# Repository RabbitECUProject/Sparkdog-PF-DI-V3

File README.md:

# Sparkdog-PF-DI-V3
KiCad project for hardware development of Sparkdog PF-DI PCB. The Sparkdog PF-DI PCB can be used as a plug in PCB for the Rabbit ECU, extending the functionality to include:

MK10 processor
4 x Direct injection driver circuit
2 x knock input circuit
1 x 4-channel H-Bridge driver
4 VVT input channels in addition to the Rabbit ECU Crank/Cam inputs

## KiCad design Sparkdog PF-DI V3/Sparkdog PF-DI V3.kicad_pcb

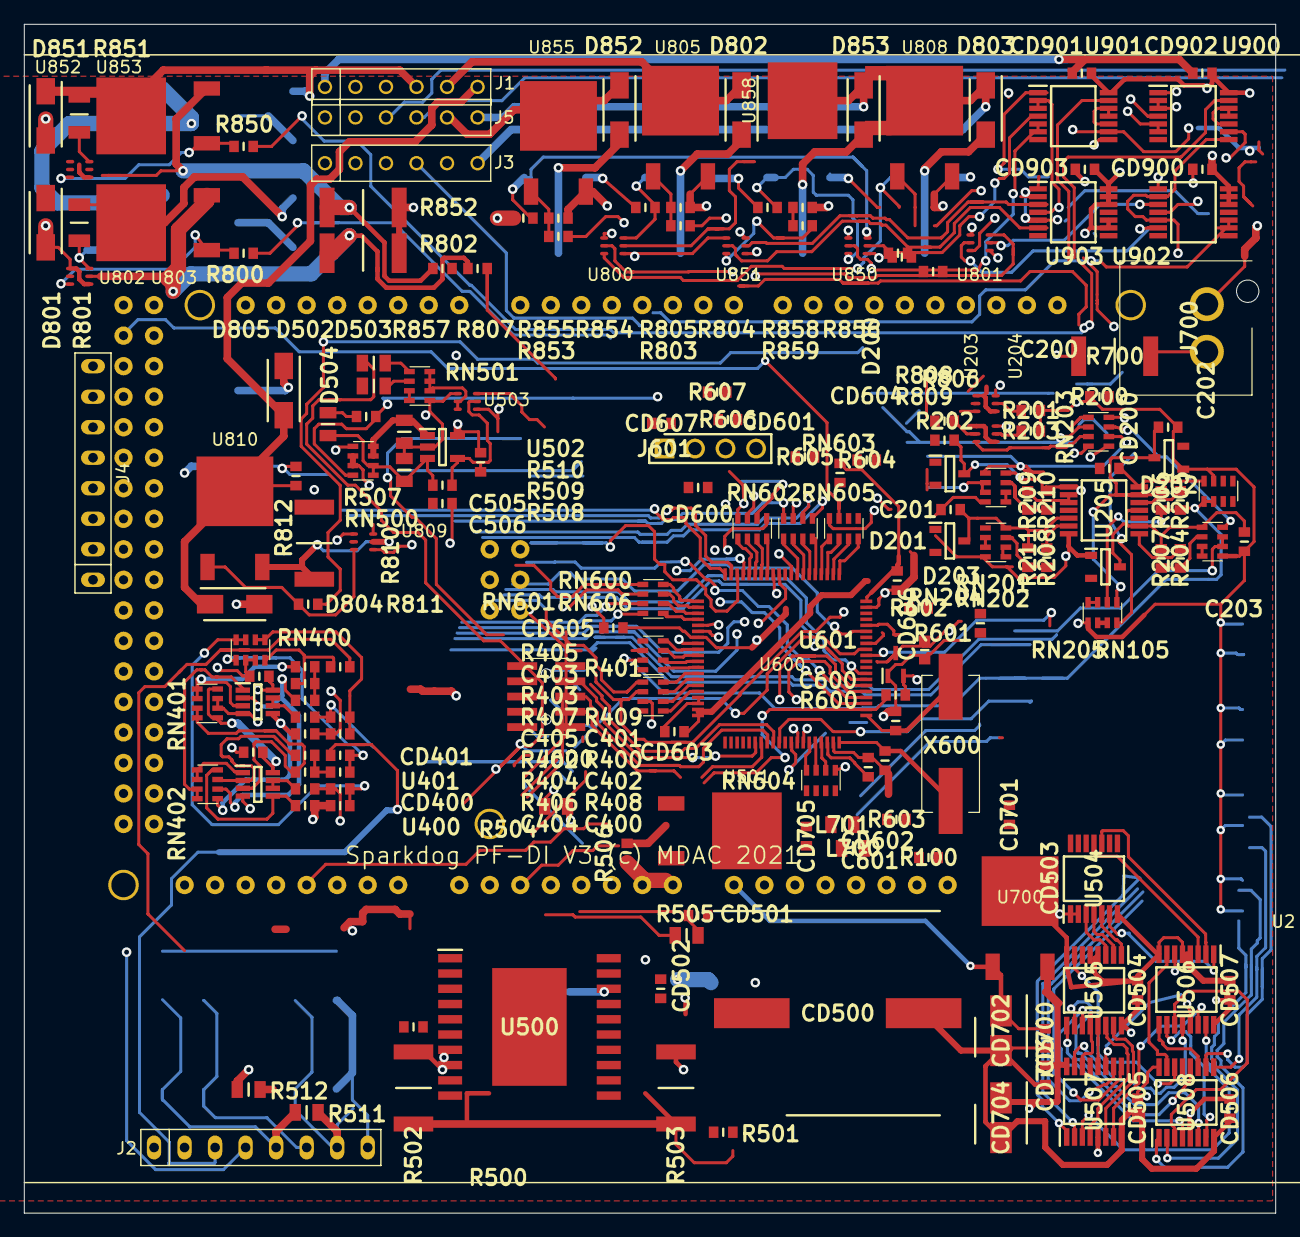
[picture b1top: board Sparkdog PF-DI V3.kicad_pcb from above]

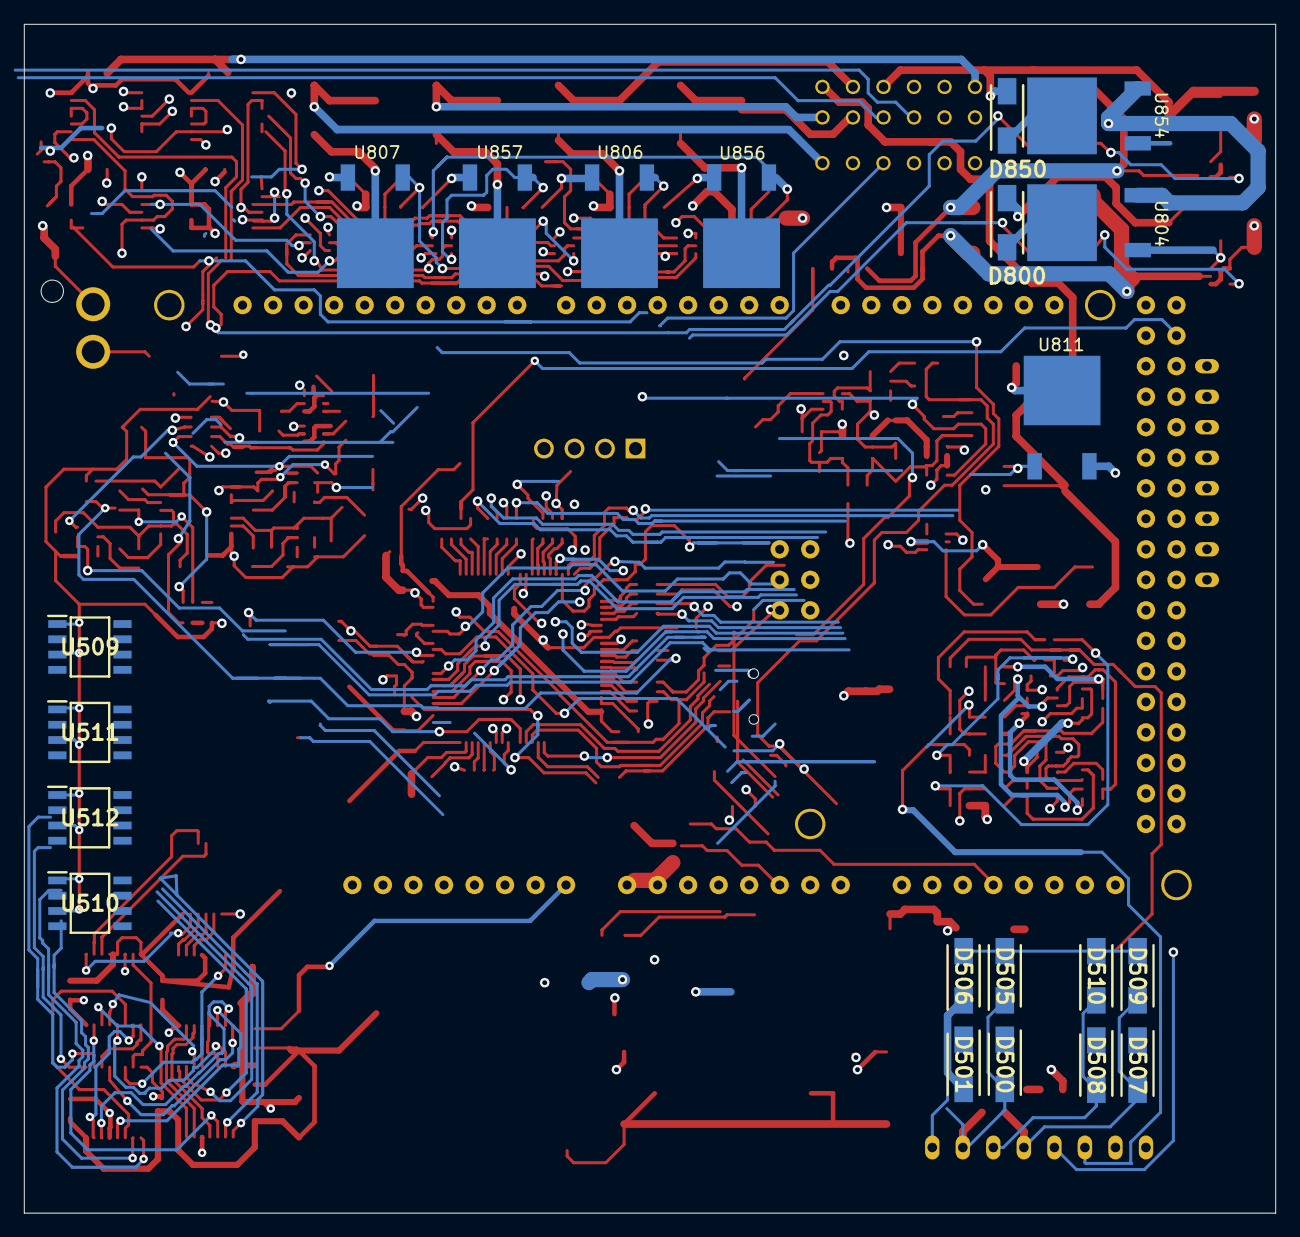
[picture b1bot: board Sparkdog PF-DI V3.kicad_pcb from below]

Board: 4 copper layers, 104.1 x 98.9 mm, 212 parts (21 on the bottom side), 251 nets.

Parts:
C200, C201, C202, C203, C402, C403, C404, C405: 0603 1nF; RESC1608X55N
C400, C401: 0603 100nF; RESC1608X55N
C505, C506: 0805 10uF; RESC2012X60N
C600, C601: 0603 10pF; RESC1608X55N
CD200, CD400, CD401, CD501, CD502, CD503, CD504, CD505, CD506, CD507, CD600, CD601, CD602, CD603, CD604, CD605, CD606, CD607, CD700, CD701, CD703, CD705, CD900, CD901, CD902, CD903: 0603 100nF; RESC1608X55N
CD500: CAP4mm 4.7uF; CAPAE1700X1700N
CD702, CD704: CAP4mm 4.7uF; CAPAE430X550N
D200, D201, D202, D203: BZX84C5V1LT1G; SOT96P237X111-3N
D500, D501, D505, D506, D507, D508, D509, D510: B120-E3; DIOM5127X229N
D502, D503, D504: 0805 1N4148; RESC2012X60N
D800, D802, D803, D805, D850, D852, D853: DO-214AC SCHOTTKY; DIOM5127X229N
D801, D804, D851: DO-214AC 81V; DIOM5127X229N
J1, J3, J5: Conn_01x06_Female; SIP-6
J2, J4: Conn_01x08_Female; SIP-8
J600: M50-3610542R; M503610542
J601: Conn_01x04; HDRV4W62P0X254_1X4_1016X240X949P
J700: Conn_01x02; 18772852
L700, L701: 0805 10nH; RESC2012X60N
R100, R204, R205, R206, R207, R208, R209, R210, R211, R602, R603, R604, R605: 0603 0R; RESC1608X55N
R200, R201, R202, R203, R406, R407, R408, R409, R600, R601, R807, R857: 0603 1k; RESC1608X55N
R400, R401, R804, R806, R854, R856: 0603 4.7k; RESC1608X55N
R402, R403, R404, R405, R507: 0603 47k; RESC1608X55N
R500, R501: 0603 100k; RESC1608X55N
R502, R503: 2512 0.1R; RESC6331X75N
R504, R505, R511, R512: 0805 0R; RESC2012X60N
R506, R803, R805, R808, R809, R812, R853, R855, R858, R859: 0603 10k; RESC1608X55N
R508: 0603 820k; RESC1608X55N
R509: 0603 5M; RESC1608X55N
R510: 0603 470k; RESC1608X55N
R606, R607: 0603 39R; RESC1608X55N
R700: 2512 1R; RESC6331X75N
R800, R850: 0603 470R; RESC1608X55N
R801, R851: 1206 4.7k; RESC3216X60N
R802, R852: 2512 0.05R; RESC6331X75N
R810: 2512 0.2R; RESC6331X75N
R811: 0603 220R; RESC1608X55N
RN105, RN604: 1206 1k; 742C083103JP
RN201, RN202, RN204, RN205, RN501, RN600, RN602, RN603, RN605, RN606: 1206 10k; 742C083103JP
RN203: 1206 470R; 742C083103JP
RN400, RN402: 220k; 742C083103JP
RN401: 220R; 742C083103JP
RN500: 1206 180k; 742C083103JP
RN601: 1206 100k; 742C083103JP
U2: Arduino_Footprint; ARDUINO_DUE
U203, U204: Dual_Trans_Array_PNP; SOT-363-6
U205: 74AHC14PW,118; SOP65P640X110-14N
U400, U401: TLV9052; SOT65P280X110-8N
U500: L298P; SOIC127P1420X360-21N
U501, U805, U806, U807, U808, U855, U856, U857, U858: SUD19P06-60; MDAC-TO-252-3
U502: TL331SN4T3G; SOT95P275X110-5N
U503, U809: Dual_Trans_Array_NPN; SOT-363-6
U504: SN74HCS164QPWRQ1; SOP65P640X120-14N
U505, U506: 74HC238PW-Q100J; SOP65P640X110-16N
U507, U508: CD4043BPWR; SOP65P640X120-16N
U509, U510, U511, U512: ZXMS6004DN8-13; SOIC127P600X175-8N
U600: MK10DX128VLK7
U601: TLV809EA29DCKR; SOT65P210X110-3N
U700: BD433M5FP-CE2; MDAC-TO-252-3
U800, U801, U802, U850, U851, U852: DDC113TU; SOT-363-6
U803, U804, U810, U811, U853, U854: STD7NK40Z; MDAC-TO-252-3
U900, U901: SN74AHCT02; SOP65P640X110-14N
U902, U903: SN74AHCT08; SOP65P640X110-14N
X600: Crystal; ECS49205PXTR

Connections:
/5 ETC/ETC_ENA: D502.2, R500.2, U600.52
/5 ETC/ETC_ENB: D503.2, R501.1, U600.71
/5 ETC/ETC_PEN: R506.2, U501.1, U503.6
/5 ETC/IO_PWM1: U509.7, U509.8
/5 ETC/IO_PWM2: U509.5, U509.6
/5 ETC/IO_PWM3: U510.7, U510.8
/5 ETC/IO_PWM4: U510.5, U510.6
/5 ETC/IO_PWM5: U511.7, U511.8
/5 ETC/IO_PWM6: U511.5, U511.6
/5 ETC/IO_PWM7: U512.7, U512.8
/5 ETC/IO_PWM8: U512.5, U512.6
/5 ETC/PIN1: U507.1, U509.2
/5 ETC/PIN2: U507.2, U509.4
/5 ETC/PIN3: U508.1, U510.2
/5 ETC/PIN4: U508.2, U510.4
/5 ETC/PIN5: U507.10, U511.2
/5 ETC/PIN6: U507.9, U511.4
/5 ETC/PIN7: U508.10, U512.2
/5 ETC/PIN8: U508.9, U512.4
/5 ETC/QA: U504.3, U505.3
/5 ETC/QB: U504.4, U505.2
/5 ETC/QC: U504.5, U505.1
/5 ETC/QD: U504.6, U506.1
/5 ETC/QE: U504.10, U506.2
/5 ETC/QF: U504.11, U506.3
/5 ETC/RES1: U506.15, U507.3
/5 ETC/RES2: U506.14, U507.7
/5 ETC/RES3: U506.13, U507.11
/5 ETC/RES4: U506.12, U507.15
/5 ETC/RES5: U506.11, U508.3
/5 ETC/RES6: U506.10, U508.7
/5 ETC/RES7: U506.9, U508.11
/5 ETC/RES8: U506.7, U508.15
/5 ETC/SET1: U505.14, U507.4
/5 ETC/SET2: U505.15, U507.6
/5 ETC/SET3: U505.13, U507.12
/5 ETC/SET4: U505.12, U507.14
/5 ETC/SET5: U505.11, U508.4
/5 ETC/SET6: U505.10, U508.6
/5 ETC/SET7: U505.9, U508.12
/5 ETC/SET8: U505.7, U508.14
/6 ETC PROCESSOR/A12: RN105.1, RN105.2, RN606.3
/6 ETC PROCESSOR/EZP_DI: J600.8, U600.27
/6 ETC PROCESSOR/GDI_LR: RN604.5, U600.72
/6 ETC PROCESSOR/GP14: R602.1, U600.50
/6 ETC PROCESSOR/GP15: R603.1, U600.49
/6 ETC PROCESSOR/GP16: R604.2, U600.69
/6 ETC PROCESSOR/GP17: R605.2, U600.70
/6 ETC PROCESSOR/RESET: J600.10, R600.2, U600.42
/6 ETC PROCESSOR/SWCLK: J600.4, U600.26
/6 ETC PROCESSOR/SWDIO: J600.2, U600.29
/6 ETC PROCESSOR/SWO: J600.6, U600.28
/8 GDI/SIG_12V_HSSA: R805.2, U800.6, U806.1
/8 GDI/SIG_12V_HSSB: R808.2, U800.3, U807.1
/8 GDI/SIG_12V_HSSC: R855.2, U850.6, U856.1
/8 GDI/SIG_12V_HSSD: R858.2, U850.3, U857.1
/8 GDI/SIG_HV_HSSA: R803.1, R804.2, U805.1
/8 GDI/SIG_HV_HSSB: R806.2, R809.1, U808.1
/8 GDI/SIG_HV_HSSC: R853.1, R854.2, U855.1
/8 GDI/SIG_HV_HSSD: R856.2, R859.1, U858.1
/8 GDI/SIG_PUMP_PWMS: R811.2, U902.8
/8 GDI/SIG_PWM_LSAB_s: R800.1, U802.3, U803.1
/8 GDI/SIG_PWM_LSCD_s: R850.1, U852.3, U853.1
/9 GDI CONTROL/SIGAB_LS_EN: R800.2, U900.13
/9 GDI CONTROL/SIGA_HV_EN: U801.2, U902.6
/9 GDI CONTROL/SIGB_HV_EN: U801.5, U902.3
/9 GDI CONTROL/SIGB_LV_EN: U800.5, U900.4
/9 GDI CONTROL/SIGCD_LS_EN: R850.2, U901.13
/9 GDI CONTROL/SIGC_HV_EN: U851.2, U903.6
/9 GDI CONTROL/SIGD_HV_EN: U851.5, U903.3
/9 GDI CONTROL/SIGD_LV_EN: U850.5, U901.4
/ACH: RN601.1, U2.11
/ACL: RN601.2, U2.12
/ATS: RN605.6, U2.14
/BATT: RN600.3, U2.19
/CTS: RN605.5, U2.13
/DCH: RN601.3, U2.9
/DCL: RN601.4, U2.10
/ETC_1A: R504.1, U500.7, U600.43
/ETC_1B: R505.1, U500.13, U600.44
/ETC_2A: R504.2, U500.9, U505.6, U600.77
/ETC_2B: R505.2, U500.15, U506.6, U600.78
/ETC_IFA: R502.1, U500.2, U600.45
/ETC_IFB: R503.1, U500.19, U600.46
/ETC_O1A: D507.2, D509.1, J2.5, R511.1, U500.4
/ETC_O1B: D508.2, D510.1, J2.6, R512.1, U500.5
/ETC_O2A: D500.2, D505.1, J2.7, R511.2, U500.16
/ETC_O2B: D501.2, D506.1, J2.8, R512.2, U500.17
/GDI1_SIG_s: U2.82, U600.79, U802.2
/GDI2_SIG_s: U2.81, U600.80, U852.2
/IEN: RN603.6, U2.42
/M1EN: RN603.7, U2.58
/M2EN: RN603.8, U2.56
/MOSI: RN604.3, U504.1, U504.2
/PPSM: RN500.1, RN600.4, U2.20
/PPSS: RN605.8, U2.16
/PUAEN: RN602.5, U2.51
/PUBEN: RN602.6, U2.36
/PUMP_PWM: D804.1, D805.2, J1.6, R812.2, U810.2
/PWIOA+: D802.1, J1.5, U805.2
/PWIOAB-: D800.2, D801.1, J1.3, R801.1, U803.2
/PWIOB+: D803.1, J3.6, U808.2
/PWIOC+: D852.1, J5.5, U855.2
/PWIOCD-: D850.2, D851.1, J1.4, R851.1, U853.2
/PWIOD+: D853.1, J5.6, U858.2
/RPS: RN600.2, U2.18
/SCLK: RN604.1, U504.8
/SIGAB_HVEN: U600.30, U900.2, U900.3, U902.4
/SIGAB_IF: R807.2, U600.47
/SIGAB_LVEN: U600.33, U800.2, U900.5, U900.6
/SIGAB_PEAK: U600.56, U900.8, U902.2, U902.5
/SIGAB_PWM: U600.57, U900.9
/SIGCD_HVEN: U600.32, U901.2, U901.3, U903.4
/SIGCD_IF: R857.2, U600.48
/SIGCD_LVEN: U600.34, U850.2, U901.5, U901.6
/SIGCD_PEAK: U600.58, U901.8, U903.2, U903.5
/SIGCD_PWM: U600.53, U901.9
/SIG_GDIP_EN: U902.9, U902.10
/SIG_K1IN: J2.3, R400.2
/SIG_K1O: R406.1, R408.2, RN606.1
/SIG_K2IN: J2.4, R401.2
/SIG_K2O: R407.1, R409.2, RN606.2
/SIG_PUMP_IF: R810.2, U600.55, U809.5, U810.3
/SIG_VVT1_IN: RN201.2, RN201.3, U2.29
/SIG_VVT2_IN: RN202.2, RN202.3, U2.30
/SIG_VVT3_IN: RN204.6, RN204.7, U2.31
/SIG_VVT4_IN: RN205.6, RN205.7, U2.32, U600.22
/TPSM: R507.1, RN500.4, RN600.1, U2.17
/TPSS: RN605.7, U2.15
/VRAEN: RN602.7, U2.34
/VRBEN: RN602.8, U2.33
/VSDC: RN606.4, U2.27
/VVT_INP1: J3.3, RN201.1, RN203.2
/VVT_INP2: J3.4, RN202.1, RN203.1
/VVT_INP3: J5.3, RN203.4, RN204.8
/VVT_INP4: J5.4, RN203.3, RN205.8
unnamed: C200.2, D200.3, R210.1, RN201.8, U205.1
unnamed: C201.1, D201.3, R211.1, RN202.8, U205.5
unnamed: C202.2, D202.3, R206.2, RN204.1, U205.13
unnamed: C203.1, D203.3, R207.1, RN205.1, U205.9, U205.11
unnamed: C400.1, R408.1, RN400.7, RN400.8
unnamed: C401.2, R409.1, RN400.5, RN400.6
unnamed: C402.1, R402.1, R404.2
unnamed: C402.2, R400.1, RN400.1
unnamed: C403.1, R403.2, R405.2
unnamed: C403.2, R401.1, RN400.4
unnamed: C404.2, RN402.8, U400.5
unnamed: C405.2, RN402.5, U401.5
unnamed: C505.2, RN500.7, RN500.8, U502.1
unnamed: C506.1, D504.2, R508.1, R509.2, RN500.5, RN500.6, U502.3
unnamed: C600.2, U600.41, X600.1
unnamed: C601.2, U600.40, X600.2
unnamed: CD500.1, CD501.2, U500.6, U501.2
unnamed: CD607.2, RN606.6, U600.11
unnamed: D502.1, RN501.1
unnamed: D503.1, RN501.2
unnamed: D504.1, R507.2
unnamed: D800.1, U804.2
unnamed: D802.2, U806.2
unnamed: D803.2, U807.2
unnamed: D805.1, U811.2
unnamed: D850.1, U854.2
unnamed: D852.2, U856.2
unnamed: D853.2, U857.2
unnamed: J601.2, R607.1
unnamed: J601.3, R606.1
unnamed: J601.4, RN606.5, U600.12
unnamed: J700.2, R700.2
unnamed: R100.1, U2.4
unnamed: R200.2, U203.5
unnamed: R201.2, U203.2
unnamed: R202.1, U204.5
unnamed: R203.1, U204.2
unnamed: R204.1, U205.8
unnamed: R204.2, R207.2, RN205.2
unnamed: R205.1, U205.12
unnamed: R205.2, R206.1, RN204.2
unnamed: R208.1, R211.2, RN202.7
unnamed: R208.2, U205.6
unnamed: R209.1, R210.2, RN201.7
unnamed: R209.2, U205.2, U205.3
unnamed: R402.2, RN402.7, U400.2
unnamed: R403.1, RN402.6, U401.2
unnamed: R404.1, RN401.7, RN401.8, U400.3
unnamed: R405.1, RN401.5, RN401.6, U401.3
unnamed: R406.2, U400.6, U400.7
unnamed: R407.2, U401.6, U401.7
unnamed: R500.1, U500.8
unnamed: R501.2, U500.14
unnamed: R509.1, R510.2, U502.4, U503.5
unnamed: R601.1, U600.51
unnamed: R606.2, RN606.7, U600.10
unnamed: R607.2, RN606.8, U600.9
unnamed: R801.2, U802.6, U804.1
unnamed: R802.2, R807.1, U802.5, U803.3
unnamed: R803.2, U801.6
unnamed: R809.2, U801.3
unnamed: R811.1, U809.3, U810.1
unnamed: R812.1, U809.6, U811.1
unnamed: R851.2, U852.6, U854.1
unnamed: R852.2, R857.1, U852.5, U853.3
unnamed: R853.2, U851.6
unnamed: R859.2, U851.3
unnamed: RN201.5, RN201.6
unnamed: RN202.5, RN202.6
unnamed: RN203.5, U204.6
unnamed: RN203.6, U204.3
unnamed: RN203.7, U203.6
unnamed: RN203.8, U203.3
unnamed: RN204.3, RN204.4
unnamed: RN205.3, RN205.4
unnamed: RN402.1, RN402.2, U400.1
unnamed: RN402.3, RN402.4, U401.1
unnamed: RN501.3, RN501.4
unnamed: RN501.6, RN501.7, RN501.8, U503.2, U503.3
unnamed: RN600.5, U600.4
unnamed: RN600.6, U600.3
unnamed: RN600.7, U600.2
unnamed: RN600.8, U600.1
unnamed: RN601.5, U600.16
unnamed: RN601.6, U600.15
unnamed: RN601.7, U600.14
unnamed: RN601.8, U600.13
unnamed: RN602.1, U600.76
unnamed: RN602.2, U600.75
unnamed: RN602.3, U600.74
unnamed: RN602.4, U600.73
unnamed: RN603.1, U600.64
unnamed: RN603.2, U600.63
unnamed: RN603.3, U600.62
unnamed: RN603.4, U600.61
unnamed: RN604.6, U600.37
unnamed: RN604.7, U600.36
unnamed: RN604.8, U600.35
unnamed: RN605.1, U600.68
unnamed: RN605.2, U600.67
unnamed: RN605.3, U600.66
unnamed: RN605.4, U600.65
unnamed: U900.1, U902.1
unnamed: U900.10, U900.11, U900.12
unnamed: U901.1, U903.1
unnamed: U901.10, U901.11, U901.12
VCC3V3: CD400.1, CD401.1, CD503.1, CD504.1, CD505.1, CD506.1, CD507.1, CD600.1, CD601.2, CD602.1, CD604.1, CD605.2, CD606.1, CD701.2, CD703.2, CD704.1, J600.1, L701.2, R100.2, R602.2, R605.1, RN401.1, RN401.4, U400.8, U401.8, U504.9, U504.14, U505.16, U506.16, U507.5, U507.16, U508.5, U508.16, U600.7, U600.25, U600.38, U600.60, U601.3, U700.3
VCC5V: CD200.1, CD502.2, CD900.1, CD901.1, CD902.1, CD903.1, R510.1, RN105.8, U2.5, U2.59, U2.60, U2.92, U203.1, U203.4, U204.1, U204.4, U205.14, U500.12, U502.5, U900.14, U901.14, U902.12, U902.13, U902.14, U903.9, U903.10, U903.12, U903.13, U903.14
VCC12VP: CD700.1, CD702.1, U2.8, U700.1
VCC12VPP: D500.1, D501.1, D507.1, D508.1, J1.2, R506.1, R805.1, R808.1, R855.1, R858.1, U501.3, U804.3, U806.3, U807.3, U811.3, U854.3, U856.3, U857.3
VCC50VPP: R700.1, R804.1, R806.1, R854.1, R856.1, U805.3, U808.3, U855.3, U858.3
VCCA3V3: CD603.2, CD705.2, L701.1, U600.17, U600.18
VSS: C200.1, C201.2, C202.1, C203.2, C400.2, C401.1, C404.1, C405.1, C505.1, C506.2, C600.1, C601.1, CD200.2, CD400.2, CD401.2, CD500.2, CD501.1, CD502.1, CD503.2, CD504.2, CD505.2, CD506.2, CD507.2, CD600.2, CD601.1, CD602.2, CD604.2, CD605.1, CD606.2, CD607.1, CD700.2, CD701.1, CD702.2, CD703.1, CD704.2, CD900.2, CD901.2, CD902.2, CD903.2, D200.1, D201.1, D202.1, D203.1, D505.2, D506.2, D509.2, D510.2, D801.2, D804.2, D851.2, J1.1, J2.2, J600.3, J600.5, J600.9, J601.1, J700.1, L700.2, R200.1, R201.1, R202.2, R203.2, R502.2, R503.2, R508.2, R603.2, R604.1, R802.1, R810.1, R852.1, RN105.7, RN201.4, RN202.4, RN204.5, RN205.5, RN400.2, RN400.3, RN401.2, RN401.3, RN500.2, RN500.3, RN501.5, U2.6, U2.7, U2.25, U2.26, U2.90, U205.7, U400.4, U401.4, U500.1, U500.10, U500.11, U500.20, U502.2, U503.1, U503.4, U504.7, U505.4, U505.5, U505.8, U506.4, U506.5, U506.8, U507.8, U508.8, U509.1, U509.3, U510.1, U510.3, U511.1, U511.3, U512.1, U512.3, U600.8, U600.39, U600.59, U601.1, U700.2, U800.1, U800.4, U801.1, U801.4, U802.1, U802.4, U809.1, U809.4, U850.1, U850.4, U851.1, U851.4, U852.1, U852.4, U900.7, U901.7, U902.7, U903.7
VSSA: CD603.1, CD705.1, L700.1, U600.19, U600.20
uC_RESET: R600.1, U601.2

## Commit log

2023-03-17 Initial files add
2023-03-23 Pushing changes for backup
2023-03-27 Running changes backup
2023-03-30 Commit and push schematics PDF print
